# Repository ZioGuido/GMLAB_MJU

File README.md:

# GMLAB_MJU
# MIDI JACK USB

This is an open-source open-hardware D-I-Y Midi event processor and TRS Accessory converter based on Arduino and the Pro-Micro board.
All necessary files are included in this repository. 
Please refer to the included PDF file for details about the assembly and the programming.

Project website: www.gmlab.it

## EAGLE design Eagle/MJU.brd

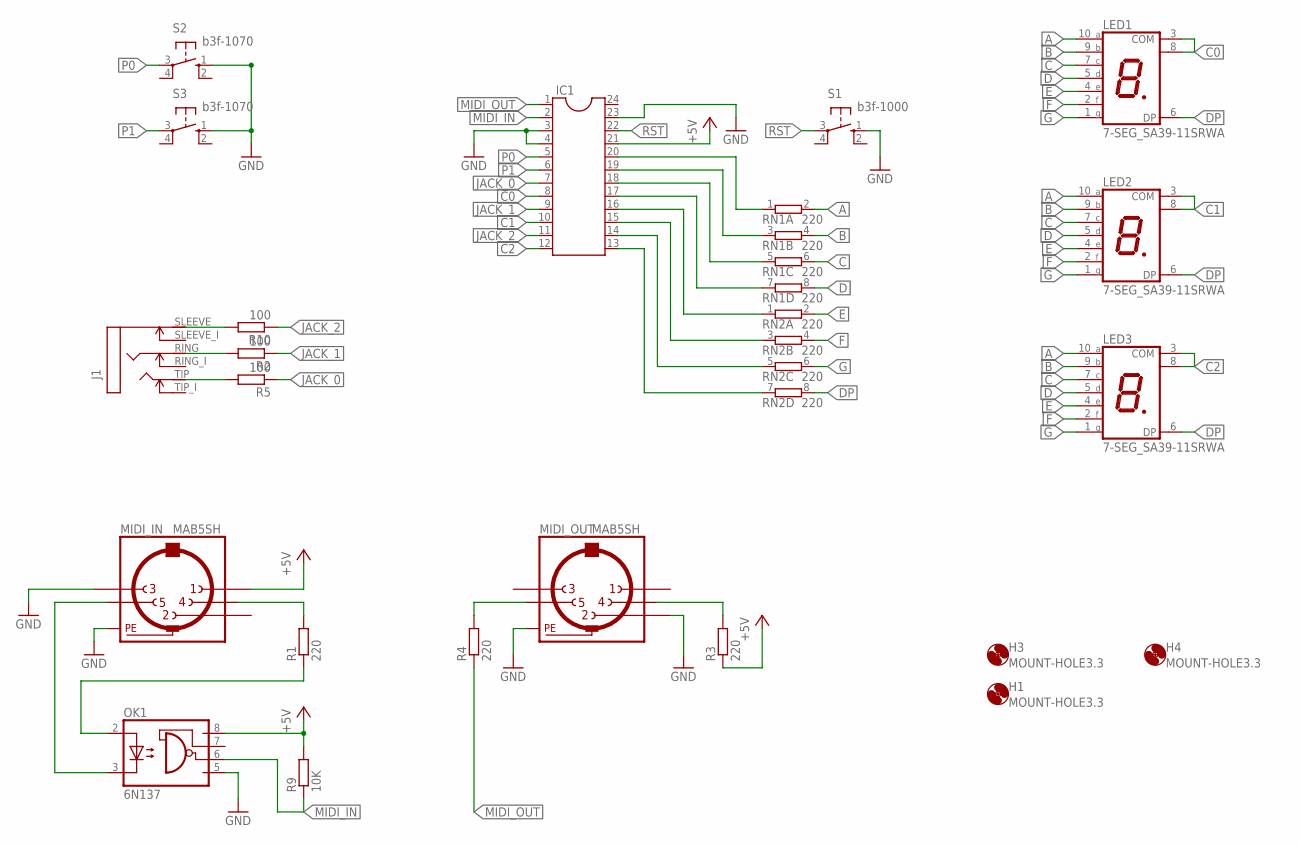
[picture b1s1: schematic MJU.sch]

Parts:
H1, H3, H4: MOUNT-HOLE3.3; 3,3
IC1: DIL24-6
J1: STEREOSWJACK_ST_TRS_INT; ST_JACK_TRS_INT
LED1, LED2, LED3: 7-SEG_SA39-11SRWA; SA39-11SRWA
MIDI_IN: MAB5SH
MIDI_OUT: MAB5SH
OK1: 6N137; DIL08
R1, R3, R4: 220; 0207/7
R2, R5, R10: 100; 0207/7
R9: 10K; 0207/7
RN1, RN2: 220; SIL8
S1: b3f-1000; B3F-10XX
S2, S3: b3f-1070; B3F-10XX

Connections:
+5V: IC1.21, MIDI_IN.1, OK1.8 (VCC), R3.1, R9.2
A: LED1.10 (A), LED2.10 (A), LED3.10 (A), RN1.2
B: LED1.9 (B), LED2.9 (B), LED3.9 (B), RN1.4 (2)
C: LED1.7 (C), LED2.7 (C), LED3.7 (C), RN1.6 (2)
C0: IC1.8, LED1.3 (COM), LED1.8 (COM)
C1: IC1.10, LED2.3 (COM), LED2.8 (COM)
C2: IC1.12, LED3.3 (COM), LED3.8 (COM)
D: LED1.5 (D), LED2.5 (D), LED3.5 (D), RN1.8 (2)
DP: LED1.6 (DP), LED2.6 (DP), LED3.6 (DP), RN2.8 (2)
E: LED1.4 (E), LED2.4 (E), LED3.4 (E), RN2.2
F: LED1.2 (F), LED2.2 (F), LED3.2 (F), RN2.4 (2)
G: LED1.1 (G), LED2.1 (G), LED3.1 (G), RN2.6 (2)
GND: IC1.3, IC1.4, IC1.23, MIDI_IN.3, MIDI_IN.PE, MIDI_IN.PE@ (PE), MIDI_OUT.2, MIDI_OUT.PE, MIDI_OUT.PE@ (PE), OK1.5 (GND), S1.1 (S), S2.1 (S), S3.1 (S)
JACK_0: IC1.7, R5.1
JACK_1: IC1.9, R2.1
JACK_2: IC1.11, R10.1
MIDI_IN: IC1.2, OK1.6 (VO), R9.1
MIDI_OUT: IC1.1, R4.1
unnamed: J1.SLEEVE (S), R10.2
unnamed: J1.RING (R), R2.2
unnamed: J1.TIP (T), R5.2
unnamed: MIDI_IN.5, OK1.3 (C)
unnamed: OK1.2 (A), R1.1
unnamed: MIDI_IN.4, R1.2
unnamed: MIDI_OUT.5, R4.2
unnamed: MIDI_OUT.4, R3.2
P0: IC1.5, S2.3
P1: IC1.6, S3.3
RST: IC1.22, S1.3
S0: IC1.20, RN1.1
S1: IC1.19, RN1.3 (1)
S2: IC1.18, RN1.5 (1)
S3: IC1.17, RN1.7 (1)
S4: IC1.16, RN2.1
S5: IC1.15, RN2.3 (1)
S6: IC1.14, RN2.5 (1)
S7: IC1.13, RN2.7 (1)

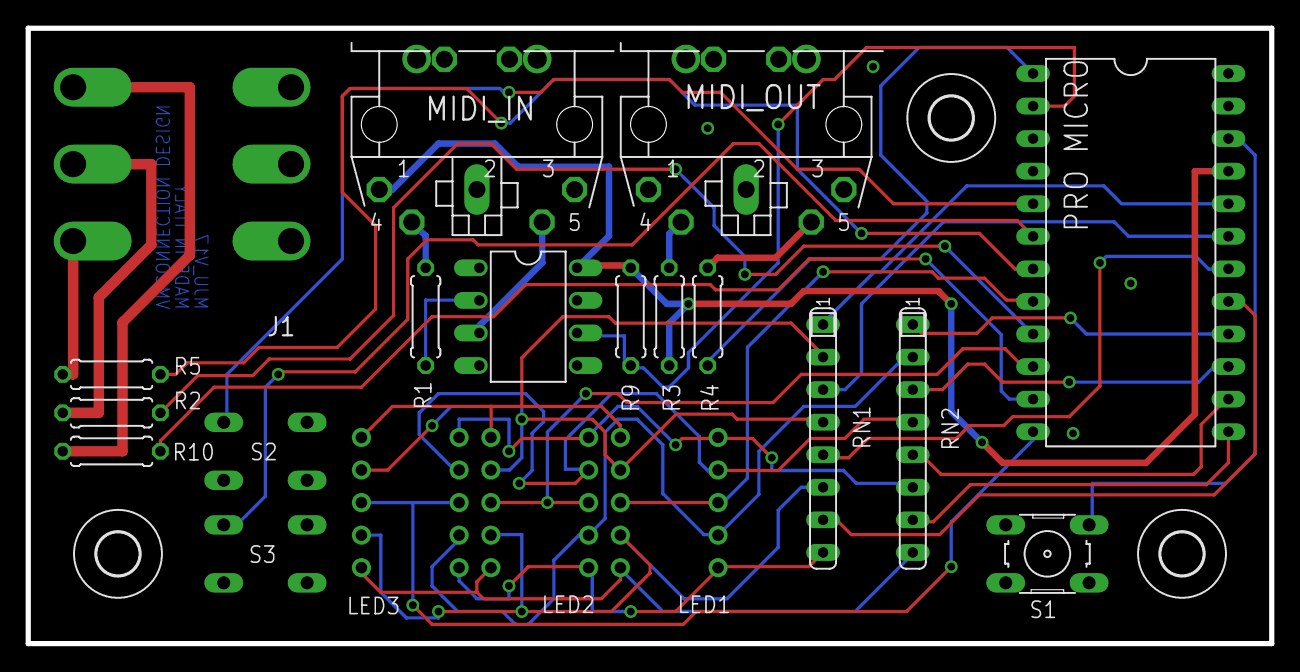
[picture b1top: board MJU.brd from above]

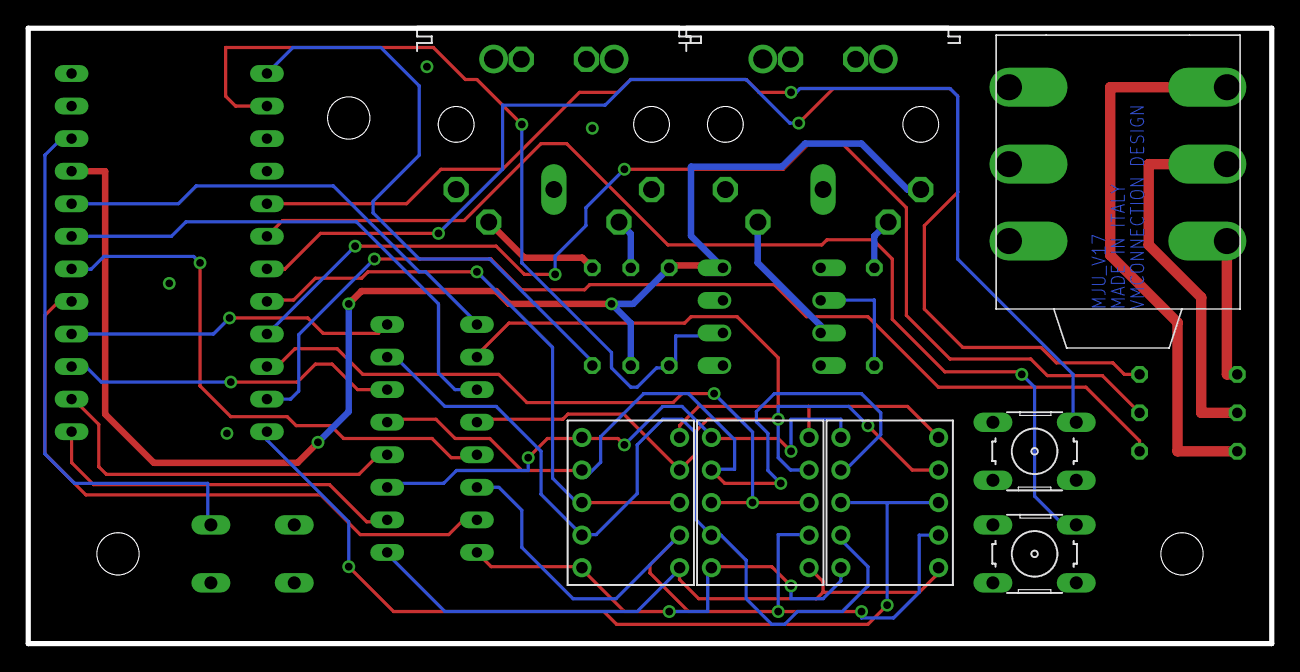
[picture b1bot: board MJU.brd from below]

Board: 2 copper layers, 97.0 x 48.0 mm, 23 parts (5 on the bottom side), 37 nets.

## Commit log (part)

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2019-04-09 Fixed minor bugs
2019-04-12 Added support for continuous sutain pedal
    Modified firmware with support for Continuous Sustain Pedal.
    Tested with Korg DS-1H.
2022-12-13 Fixed bug with transpose setting
2023-09-26 Added two more page: Range Min & Max
2024-03-18 Fix for possible hung notes with velocity on
    Added lock to avoid double note-on events with velocity on
2024-03-20 Updated date in comment
2026-04-19 Updated to use the most recent libraries
2026-04-19 Added Min & Max parameters
